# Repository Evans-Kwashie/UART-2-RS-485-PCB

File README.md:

# UART to RS-485 Converter Board

A 2-layer PCB that converts UART (TTL logic level) to RS-485 differential 
signaling, designed and routed from scratch in KiCad as a self-directed 
learning project focused on differential pair fundamentals.

## Overview

RS-485 is widely used in industrial automation, building automation, and 
long-distance serial communication where noise immunity and cable length 
matter more than raw speed. This board bridges a standard UART interface 
(TX/RX) to an RS-485 A/B differential bus using the STR485 transceiver.

## Key Design Features

- **STR485 transceiver** with DE/RE tied together and driven from a single 
  control pin for half-duplex direction switching
- **120Ω termination resistor** on the A/B bus, placed at the board's output
- **TVS diode protection** on the bus lines for ESD/surge resistance
- **Differential pair routing** for the A/B signal traces
- Standard decoupling (100nF) on the transceiver's VCC pin

## Design Challenges Solved

- Diagnosed and resolved a **thermal relief spoke count DRC error** on 
  fine-pitch pads by adjusting zone connection settings
- Worked through a **hole clearance violation** on the connector's 
  mechanical mounting holes, evaluating fab tolerance vs. board rules
- Learned and applied **differential pair routing concepts**: controlled 
  spacing, length matching, and why they matter for signal integrity at 
  higher speeds

## Files

- `.kicad_sch` / `.kicad_pcb` — full KiCad source project
- `RS 485.pdf` — schematic export
- `board_3d_render.png` — 3D rendered preview

## Tools

Designed entirely in KiCad 10.

## Status

Schematic and layout complete, DRC clean. Not yet fabricated/assembled.

## Licensing

### Hardware design

The hardware design files in this repository, including schematics, PCB layouts, manufacturing outputs and related hardware documentation, are licensed under the **CERN Open Hardware Licence Version 2 – Strongly Reciprocal (CERN-OHL-S-2.0)**. See [LICENSE](./LICENSE).

The complete source for this hardware design is available in this repository: https://github.com/Evans-Kwashie/UART-2-RS-485-PCB

### Software

Any firmware, software or code in this repository that is explicitly identified as software is licensed under the **MIT License**. See [LICENSE-MIT](./LICENSE-MIT). Third-party components remain under their respective licences.

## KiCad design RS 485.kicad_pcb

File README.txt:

# UART to RS-485 Converter Board

A 2-layer PCB that converts UART (TTL logic level) to RS-485 differential 
signaling, designed and routed from scratch in KiCad as a self-directed 
learning project focused on differential pair fundamentals.

## Overview

RS-485 is widely used in industrial automation, building automation, and 
long-distance serial communication where noise immunity and cable length 
matter more than raw speed. This board bridges a standard UART interface 
(TX/RX) to an RS-485 A/B differential bus using the STR485 transceiver.

## Key Design Features

- **STR485 transceiver** with DE/RE tied together and driven from a single 
  control pin for half-duplex direction switching
- **120Ω termination resistor** on the A/B bus, placed at the board's output
- **TVS diode protection** on the bus lines for ESD/surge resistance
- **Differential pair routing** for the A/B signal traces
- Standard decoupling (100nF) on the transceiver's VCC pin

## Design Challenges Solved

- Diagnosed and resolved a **thermal relief spoke count DRC error** on 
  fine-pitch pads by adjusting zone connection settings
- Worked through a **hole clearance violation** on the connector's 
  mechanical mounting holes, evaluating fab tolerance vs. board rules
- Learned and applied **differential pair routing concepts**: controlled 
  spacing, length matching, and why they matter for signal integrity at 
  higher speeds

## Files

- `.kicad_sch` / `.kicad_pcb` — full KiCad source project
- `RS485_Schematic.pdf` — schematic export
- `board_3d_render.png` — 3D rendered preview

## Tools

Designed entirely in KiCad 10.

## Status

Schematic and layout complete, DRC clean. Not yet fabricated/assembled.

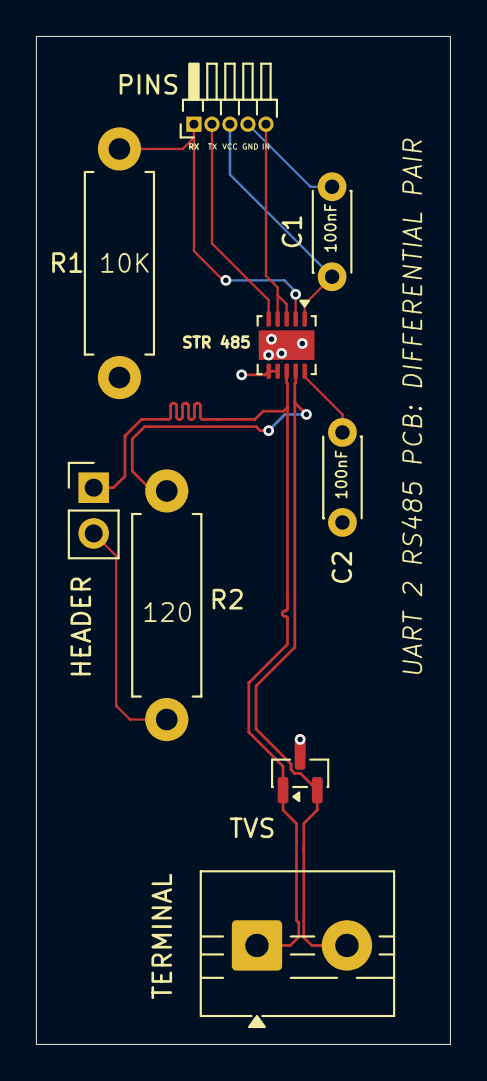
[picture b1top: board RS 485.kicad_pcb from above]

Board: 4 copper layers, 23.0 x 56.0 mm, 9 parts (0 on the bottom side), 8 nets.

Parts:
C1, C2: 100nF; C_Disc_D4.3mm_W1.9mm_P5.00mm
HEADER: Jumper_2_Open; PinHeader_1x02_P2.54mm_Vertical
PINS: Conn_01x05_Pin; PinHeader_1x05_P1.00mm_Horizontal
R1: 10K; R_Axial_DIN0411_L9.9mm_D3.6mm_P12.70mm_Horizontal
R2: 120; R_Axial_DIN0411_L9.9mm_D3.6mm_P12.70mm_Horizontal
STR 485: STR485; DFN-10-1EP_3x3mm_P0.5mm_EP1.646x3.1mm
TERMINAL: Screw_Terminal_01x02; TerminalBlock_MaiXu_MX126-5.0-02P_1x02_P5.00mm
TVS: SM712_SOT23; SOT-23

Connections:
3V3D: C1.1, C2.2, PINS.3, R1.1, STR 485.1 (VL), STR 485.10 (VCC)
/RS 485_N: R2.2, STR 485.9 (B), TERMINAL.2, TVS.2 (A2)
/RS 485_P: HEADER.1 (A), STR 485.8 (A), TERMINAL.1, TVS.1 (A1)
GNDD: C1.2, C2.1, PINS.4, STR 485.6 (GND), STR 485.7 (SLR), STR 485.11 (GND), TVS.3 (common)
IN: PINS.5, STR 485.3 (DE), STR 485.4 (~RE)
unnamed: HEADER.2 (B), R2.1
RX: PINS.1, R1.2, STR 485.2 (R)
TX: PINS.2, STR 485.5 (D)
